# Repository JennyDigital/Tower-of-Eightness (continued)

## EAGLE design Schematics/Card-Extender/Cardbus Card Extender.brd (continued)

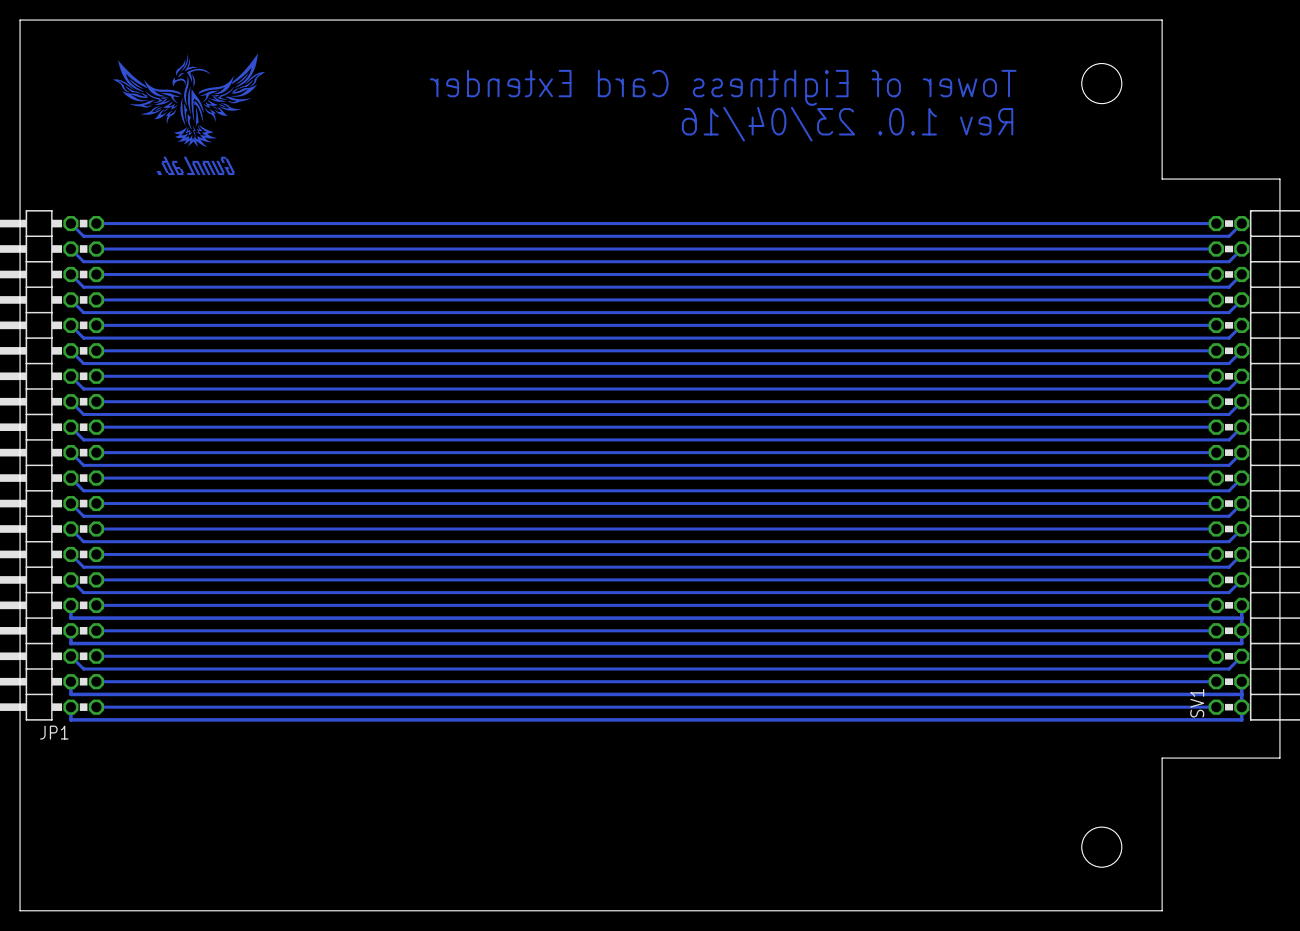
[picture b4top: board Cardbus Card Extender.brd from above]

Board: 2 copper layers, 125.7 x 88.9 mm, 3 parts (0 on the bottom side), 38 nets.

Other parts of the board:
U$1: LIONTECH

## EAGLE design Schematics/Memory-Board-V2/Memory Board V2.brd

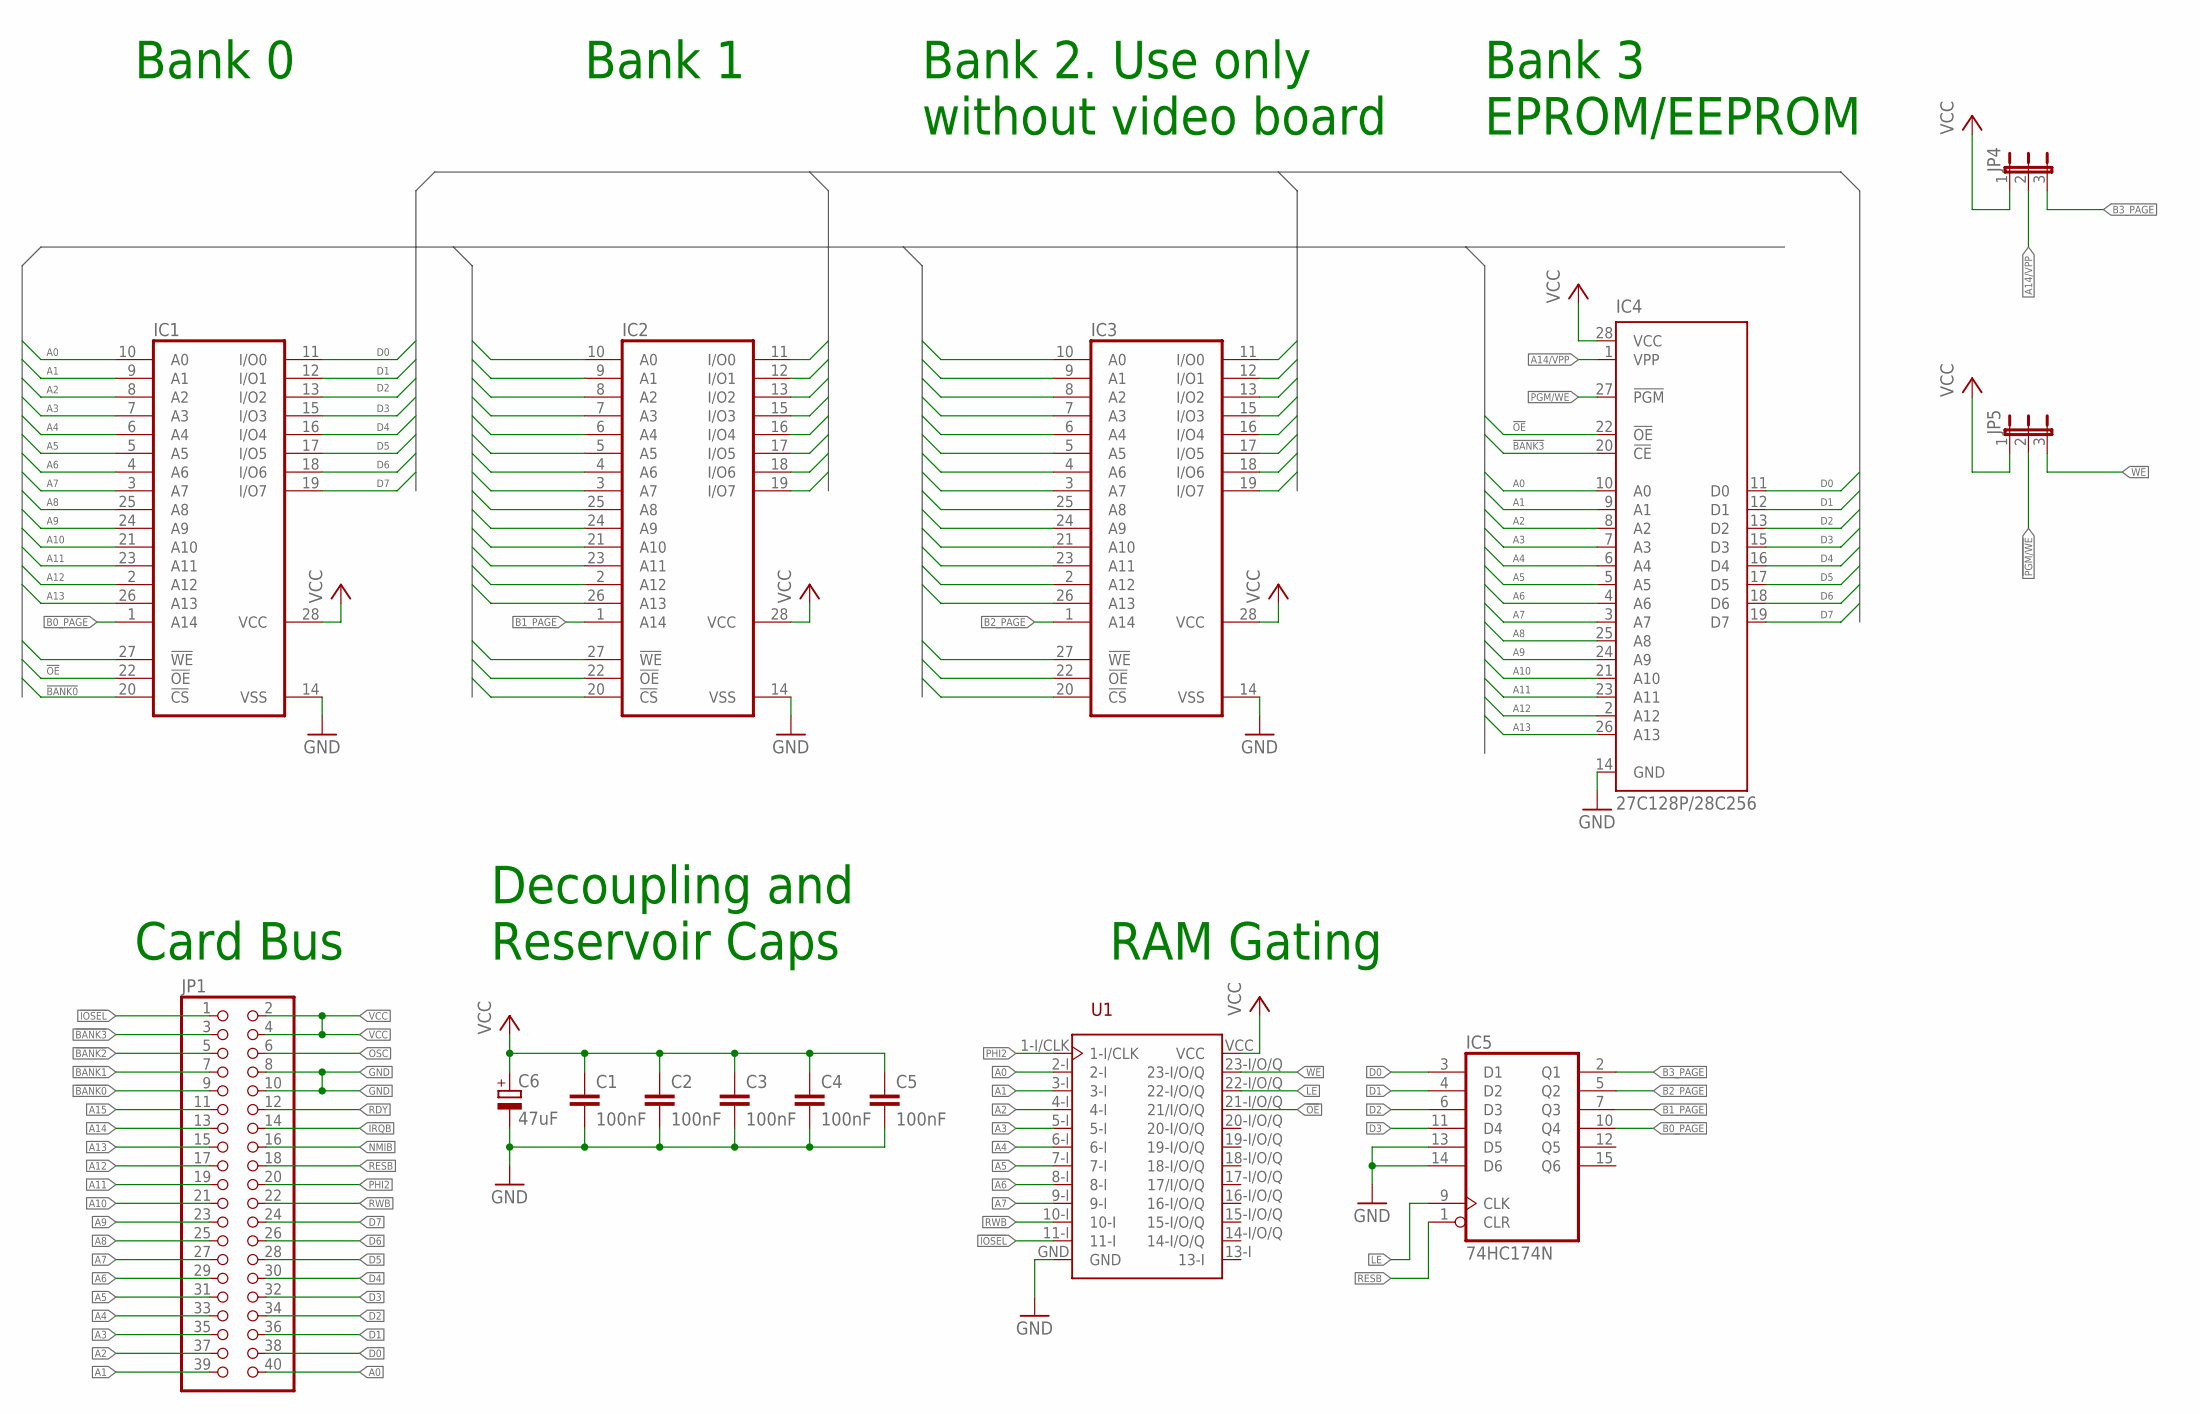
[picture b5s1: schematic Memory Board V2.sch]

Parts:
C1, C2, C3, C4, C5: 100nF; C050-025X075
C6: 47uF; E2,5-7
IC1, IC2, IC3: 62256P; DIL28-6
IC4: 27C128P/28C256; DIL28-6
IC5: 74HC174N; DIL16
JP1: PINHD-2X20/90; 2X20/90
JP4, JP5: JP2E; JP2
U1: GAL22V10D-DIP; DIP24

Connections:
!BANK0: IC1.20 (!CS), JP1.9
!BANK1: IC2.20 (!CS), JP1.7
!BANK2: IC3.20 (!CS), JP1.5
!BANK3: IC4.20 (!CE), JP1.3
!IOSEL: JP1.1, U1.11-I
!OE: IC1.22 (!OE), IC2.22 (!OE), IC3.22 (!OE), IC4.22 (!OE), U1.21-I/O/Q (21/I/O/Q)
!PGM/WE: IC4.27 (!PGM), JP5.2
!WE: IC1.27 (!WE), IC2.27 (!WE), IC3.27 (!WE), JP5.3, U1.23-I/O/Q
A0: IC1.10 (A0), IC2.10 (A0), IC3.10 (A0), IC4.10 (A0), JP1.40, U1.2-I
A1: IC1.9 (A1), IC2.9 (A1), IC3.9 (A1), IC4.9 (A1), JP1.39, U1.3-I
A2: IC1.8 (A2), IC2.8 (A2), IC3.8 (A2), IC4.8 (A2), JP1.37, U1.4-I
A3: IC1.7 (A3), IC2.7 (A3), IC3.7 (A3), IC4.7 (A3), JP1.35, U1.5-I
A4: IC1.6 (A4), IC2.6 (A4), IC3.6 (A4), IC4.6 (A4), JP1.33, U1.6-I
A5: IC1.5 (A5), IC2.5 (A5), IC3.5 (A5), IC4.5 (A5), JP1.31, U1.7-I
A6: IC1.4 (A6), IC2.4 (A6), IC3.4 (A6), IC4.4 (A6), JP1.29, U1.8-I
A7: IC1.3 (A7), IC2.3 (A7), IC3.3 (A7), IC4.3 (A7), JP1.27, U1.9-I
A8: IC1.25 (A8), IC2.25 (A8), IC3.25 (A8), IC4.25 (A8), JP1.25
A9: IC1.24 (A9), IC2.24 (A9), IC3.24 (A9), IC4.24 (A9), JP1.23
A10: IC1.21 (A10), IC2.21 (A10), IC3.21 (A10), IC4.21 (A10), JP1.21
A11: IC1.23 (A11), IC2.23 (A11), IC3.23 (A11), IC4.23 (A11), JP1.19
A12: IC1.2 (A12), IC2.2 (A12), IC3.2 (A12), IC4.2 (A12), JP1.17
A13: IC1.26 (A13), IC2.26 (A13), IC3.26 (A13), IC4.26 (A13), JP1.15
A14: JP1.13
A14/VPP: IC4.1 (VPP), JP4.2
A15: JP1.11
B0_PAGE: IC1.1 (A14), IC5.10 (Q4)
B1_PAGE: IC2.1 (A14), IC5.7 (Q3)
B2_PAGE: IC3.1 (A14), IC5.5 (Q2)
B3_PAGE: IC5.2 (Q1), JP4.3
D0: IC1.11 (I/O0), IC2.11 (I/O0), IC3.11 (I/O0), IC4.11 (D0), IC5.3 (D1), JP1.38
D1: IC1.12 (I/O1), IC2.12 (I/O1), IC3.12 (I/O1), IC4.12 (D1), IC5.4 (D2), JP1.36
D2: IC1.13 (I/O2), IC2.13 (I/O2), IC3.13 (I/O2), IC4.13 (D2), IC5.6 (D3), JP1.34
D3: IC1.15 (I/O3), IC2.15 (I/O3), IC3.15 (I/O3), IC4.15 (D3), IC5.11 (D4), JP1.32
D4: IC1.16 (I/O4), IC2.16 (I/O4), IC3.16 (I/O4), IC4.16 (D4), JP1.30
D5: IC1.17 (I/O5), IC2.17 (I/O5), IC3.17 (I/O5), IC4.17 (D5), JP1.28
D6: IC1.18 (I/O6), IC2.18 (I/O6), IC3.18 (I/O6), IC4.18 (D6), JP1.26
D7: IC1.19 (I/O7), IC2.19 (I/O7), IC3.19 (I/O7), IC4.19 (D7), JP1.24
GND: C1.2, C2.2, C3.2, C4.2, C5.2, C6.-, IC1.14 (VSS), IC2.14 (VSS), IC3.14 (VSS), IC4.14 (GND), IC5.8 (GND), IC5.13 (D5), IC5.14 (D6), JP1.8, JP1.10, U1.GND
IRQB: JP1.14
LE: IC5.9 (CLK), U1.22-I/O/Q
NMIB: JP1.16
OSC: JP1.6
PHI2: JP1.20, U1.1-I/CLK
RDY: JP1.12
RESB: IC5.1 (CLR), JP1.18
RWB: JP1.22, U1.10-I
VCC: C1.1, C2.1, C3.1, C4.1, C5.1, C6.+, IC1.28 (VCC), IC2.28 (VCC), IC3.28 (VCC), IC4.28 (VCC), IC5.16 (VCC), JP1.2, JP1.4, JP4.1, JP5.1, U1.VCC

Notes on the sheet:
Card Bus
Bank 0
Bank 3 EPROM/EEPROM
Bank 1
Bank 2. Use only without video board
Decoupling and Reservoir Caps
RAM Gating

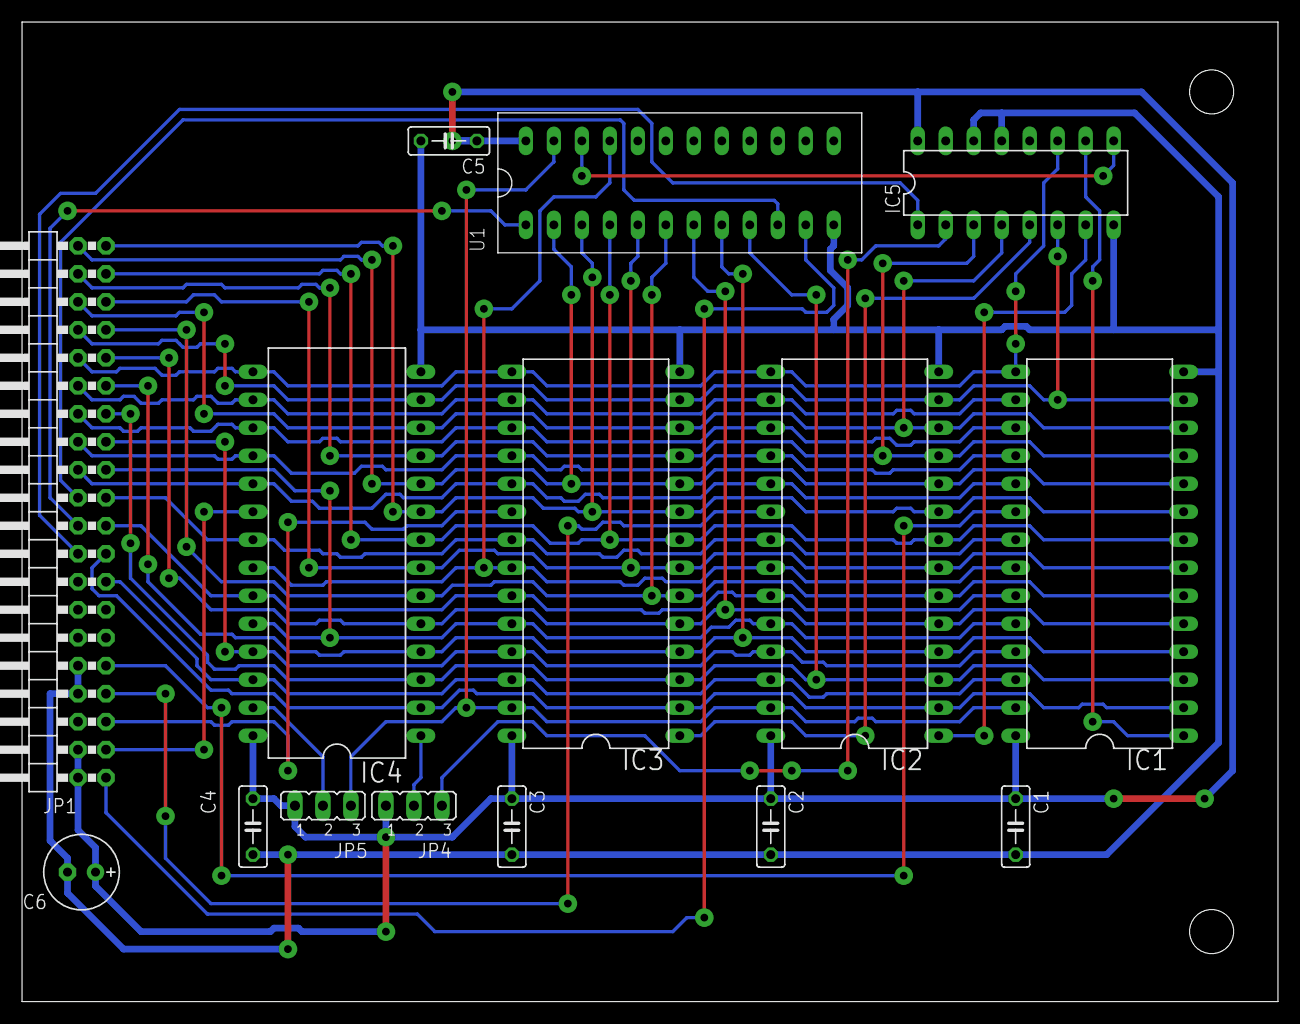
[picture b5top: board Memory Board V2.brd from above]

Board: 2 copper layers, 114.0 x 88.9 mm, 15 parts (0 on the bottom side), 41 nets.

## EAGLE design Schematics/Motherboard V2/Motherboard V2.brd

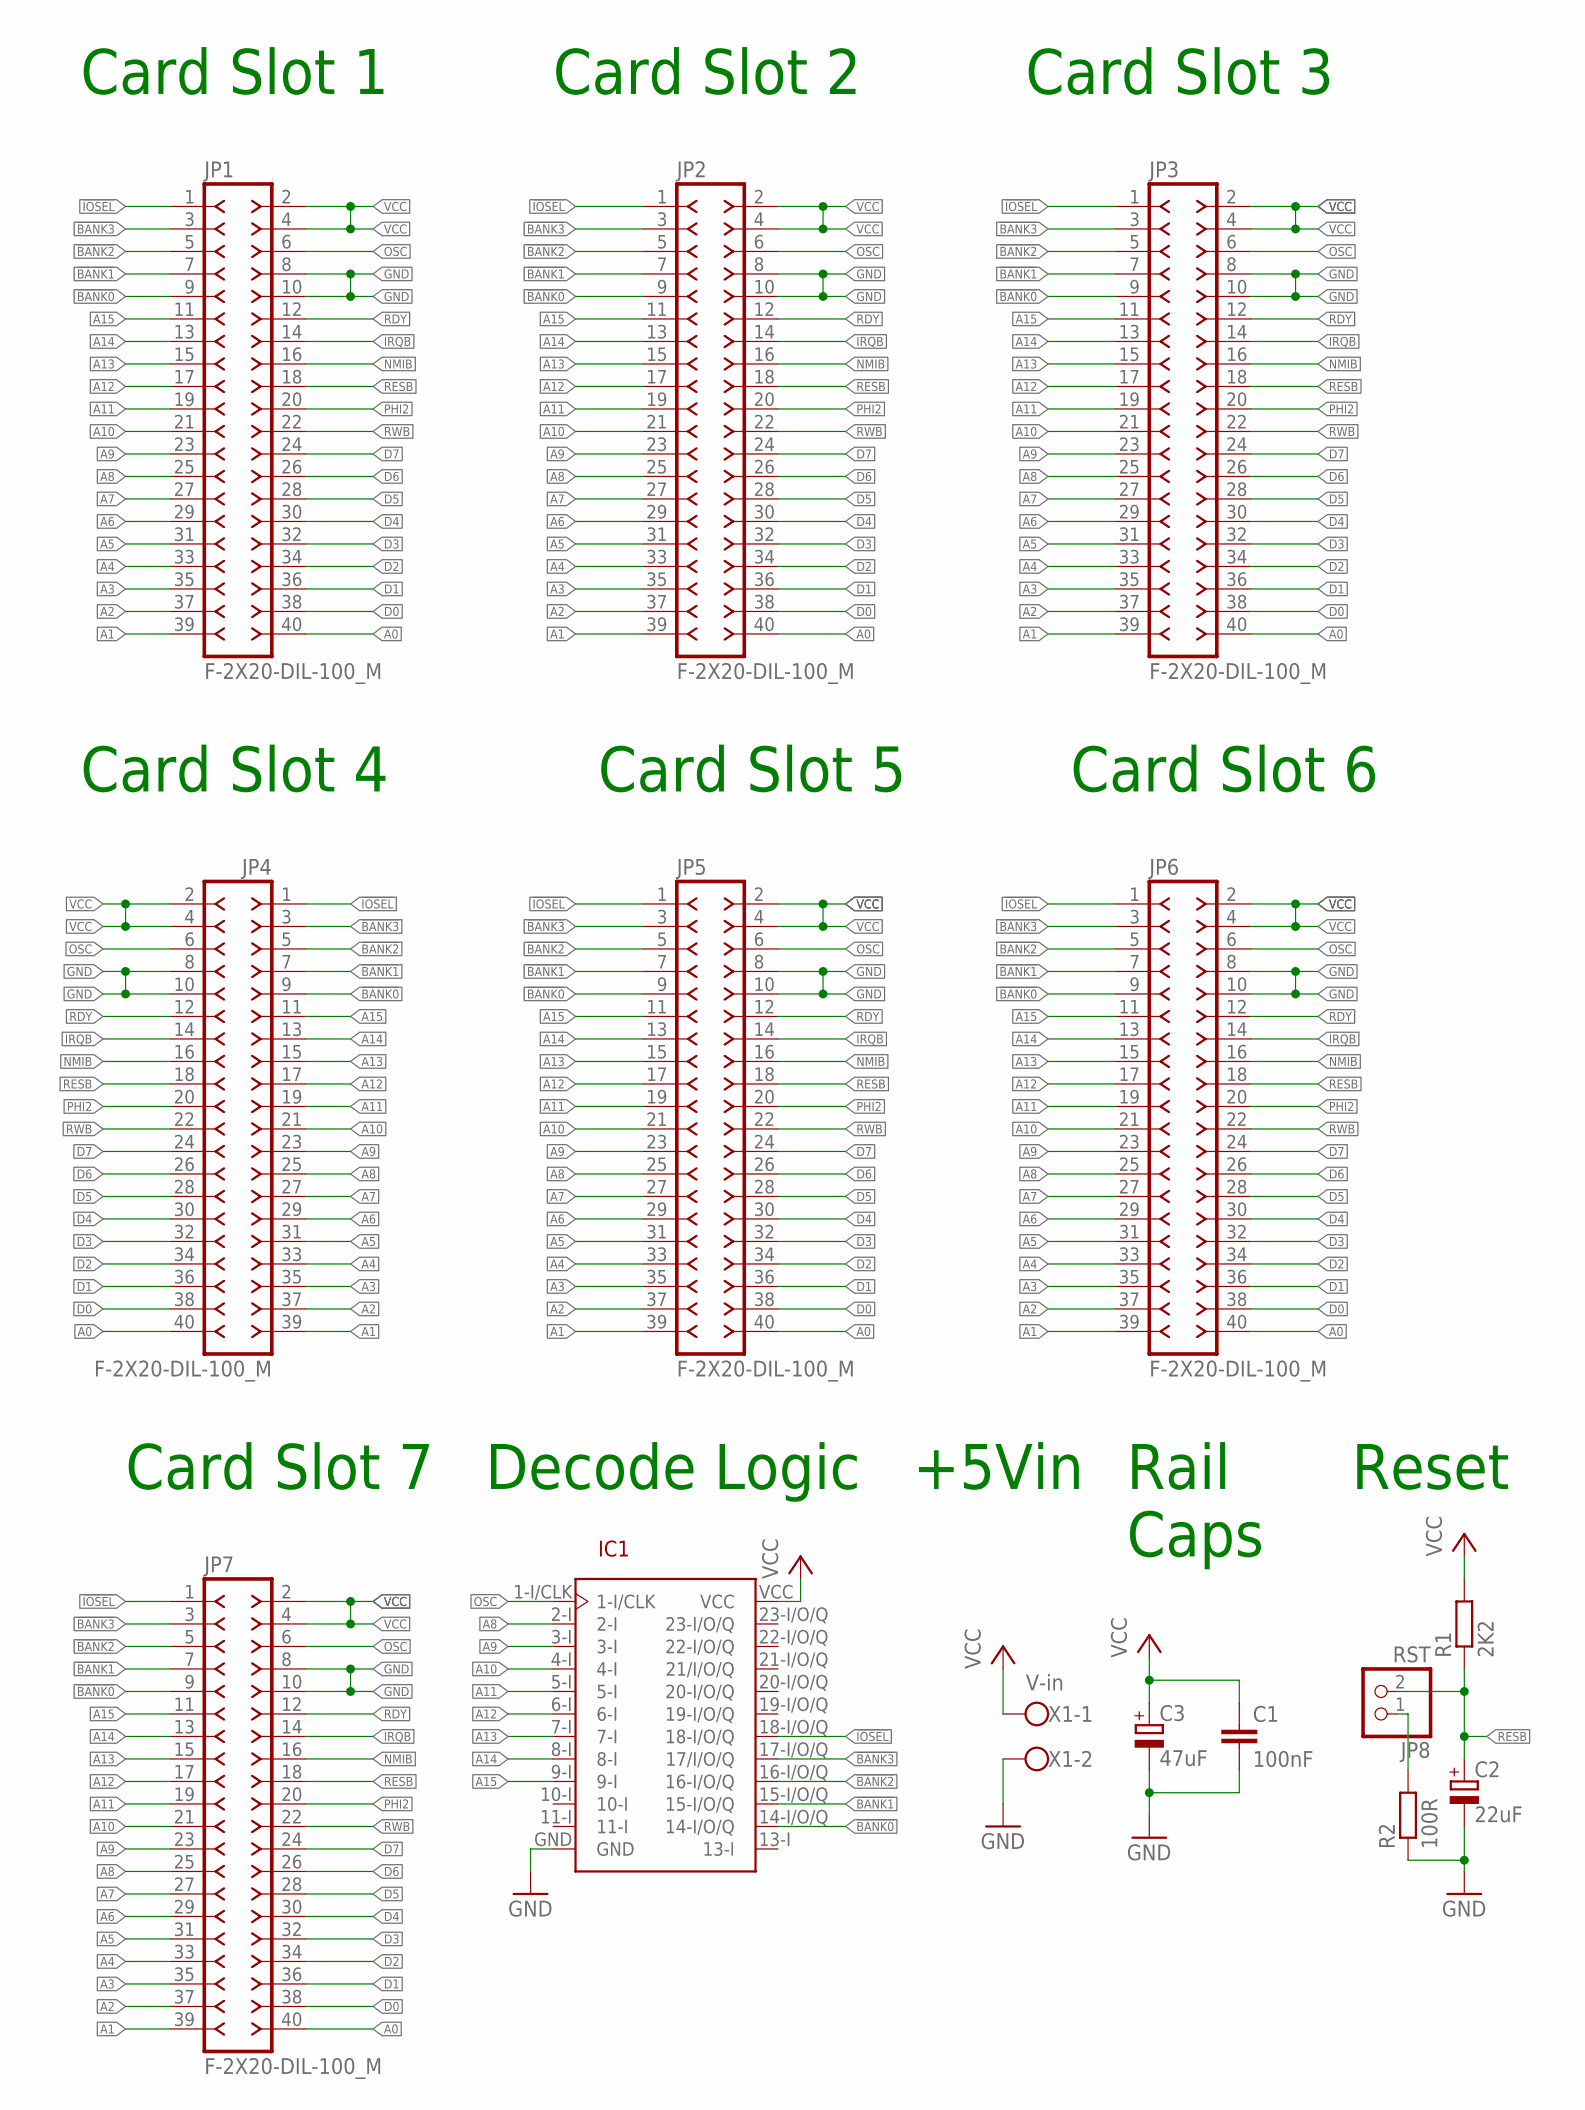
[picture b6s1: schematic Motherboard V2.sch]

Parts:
C1: 100nF; C050-025X075
C2: 22uF; E2-5
C3: 47uF; E2,5-7
IC1: GAL22V10D-DIP; DIP24
JP1, JP2, JP3, JP4, JP5, JP6, JP7: F-2X20-DIL-100_M; DIL-100-2X20_M
JP8: RST; 1X02
R1: 2K2; 0207/10
R2: 100R; 0207/10
X1: V-in; W237-102

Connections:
!BANK0: IC1.14-I/O/Q, JP1.9, JP2.9, JP3.9, JP4.9, JP5.9, JP6.9, JP7.9
!BANK1: IC1.15-I/O/Q, JP1.7, JP2.7, JP3.7, JP4.7, JP5.7, JP6.7, JP7.7
!BANK2: IC1.16-I/O/Q, JP1.5, JP2.5, JP3.5, JP4.5, JP5.5, JP6.5, JP7.5
!BANK3: IC1.17-I/O/Q (17/I/O/Q), JP1.3, JP2.3, JP3.3, JP4.3, JP5.3, JP6.3, JP7.3
!IOSEL: IC1.18-I/O/Q, JP1.1, JP2.1, JP3.1, JP4.1, JP5.1, JP6.1, JP7.1
A0: JP1.40, JP2.40, JP3.40, JP4.40, JP5.40, JP6.40, JP7.40
A1: JP1.39, JP2.39, JP3.39, JP4.39, JP5.39, JP6.39, JP7.39
A2: JP1.37, JP2.37, JP3.37, JP4.37, JP5.37, JP6.37, JP7.37
A3: JP1.35, JP2.35, JP3.35, JP4.35, JP5.35, JP6.35, JP7.35
A4: JP1.33, JP2.33, JP3.33, JP4.33, JP5.33, JP6.33, JP7.33
A5: JP1.31, JP2.31, JP3.31, JP4.31, JP5.31, JP6.31, JP7.31
A6: JP1.29, JP2.29, JP3.29, JP4.29, JP5.29, JP6.29, JP7.29
A7: JP1.27, JP2.27, JP3.27, JP4.27, JP5.27, JP6.27, JP7.27
A8: IC1.2-I, JP1.25, JP2.25, JP3.25, JP4.25, JP5.25, JP6.25, JP7.25
A9: IC1.3-I, JP1.23, JP2.23, JP3.23, JP4.23, JP5.23, JP6.23, JP7.23
A10: IC1.4-I, JP1.21, JP2.21, JP3.21, JP4.21, JP5.21, JP6.21, JP7.21
A11: IC1.5-I, JP1.19, JP2.19, JP3.19, JP4.19, JP5.19, JP6.19, JP7.19
A12: IC1.6-I, JP1.17, JP2.17, JP3.17, JP4.17, JP5.17, JP6.17, JP7.17
A13: IC1.7-I, JP1.15, JP2.15, JP3.15, JP4.15, JP5.15, JP6.15, JP7.15
A14: IC1.8-I, JP1.13, JP2.13, JP3.13, JP4.13, JP5.13, JP6.13, JP7.13
A15: IC1.9-I, JP1.11, JP2.11, JP3.11, JP4.11, JP5.11, JP6.11, JP7.11
D0: JP1.38, JP2.38, JP3.38, JP4.38, JP5.38, JP6.38, JP7.38
D1: JP1.36, JP2.36, JP3.36, JP4.36, JP5.36, JP6.36, JP7.36
D2: JP1.34, JP2.34, JP3.34, JP4.34, JP5.34, JP6.34, JP7.34
D3: JP1.32, JP2.32, JP3.32, JP4.32, JP5.32, JP6.32, JP7.32
D4: JP1.30, JP2.30, JP3.30, JP4.30, JP5.30, JP6.30, JP7.30
D5: JP1.28, JP2.28, JP3.28, JP4.28, JP5.28, JP6.28, JP7.28
D6: JP1.26, JP2.26, JP3.26, JP4.26, JP5.26, JP6.26, JP7.26
D7: JP1.24, JP2.24, JP3.24, JP4.24, JP5.24, JP6.24, JP7.24
GND: C1.2, C2.-, C3.-, IC1.GND, JP1.8, JP1.10, JP2.8, JP2.10, JP3.8, JP3.10, JP4.8, JP4.10, JP5.8, JP5.10, JP6.8, JP6.10, JP7.8, JP7.10, R2.1, X1.2
IRQB: JP1.14, JP2.14, JP3.14, JP4.14, JP5.14, JP6.14, JP7.14
unnamed: JP8.1, R2.2
NMIB: JP1.16, JP2.16, JP3.16, JP4.16, JP5.16, JP6.16, JP7.16
OSC: IC1.1-I/CLK, JP1.6, JP2.6, JP3.6, JP4.6, JP5.6, JP6.6, JP7.6
PHI2: JP1.20, JP2.20, JP3.20, JP4.20, JP5.20, JP6.20, JP7.20
RDY: JP1.12, JP2.12, JP3.12, JP4.12, JP5.12, JP6.12, JP7.12
RESB: C2.+, JP1.18, JP2.18, JP3.18, JP4.18, JP5.18, JP6.18, JP7.18, JP8.2, R1.1
RWB: JP1.22, JP2.22, JP3.22, JP4.22, JP5.22, JP6.22, JP7.22
VCC: C1.1, C3.+, IC1.VCC, JP1.2, JP1.4, JP2.2, JP2.4, JP3.2, JP3.4, JP4.2, JP4.4, JP5.2, JP5.4, JP6.2, JP6.4, JP7.2, JP7.4, R1.2, X1.1

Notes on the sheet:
Decode Logic
Card Slot 1
Card Slot 2
Card Slot 3
Card Slot 4
Reset
+5Vin
Rail Caps
Card Slot 5
Card Slot 6
Card Slot 7

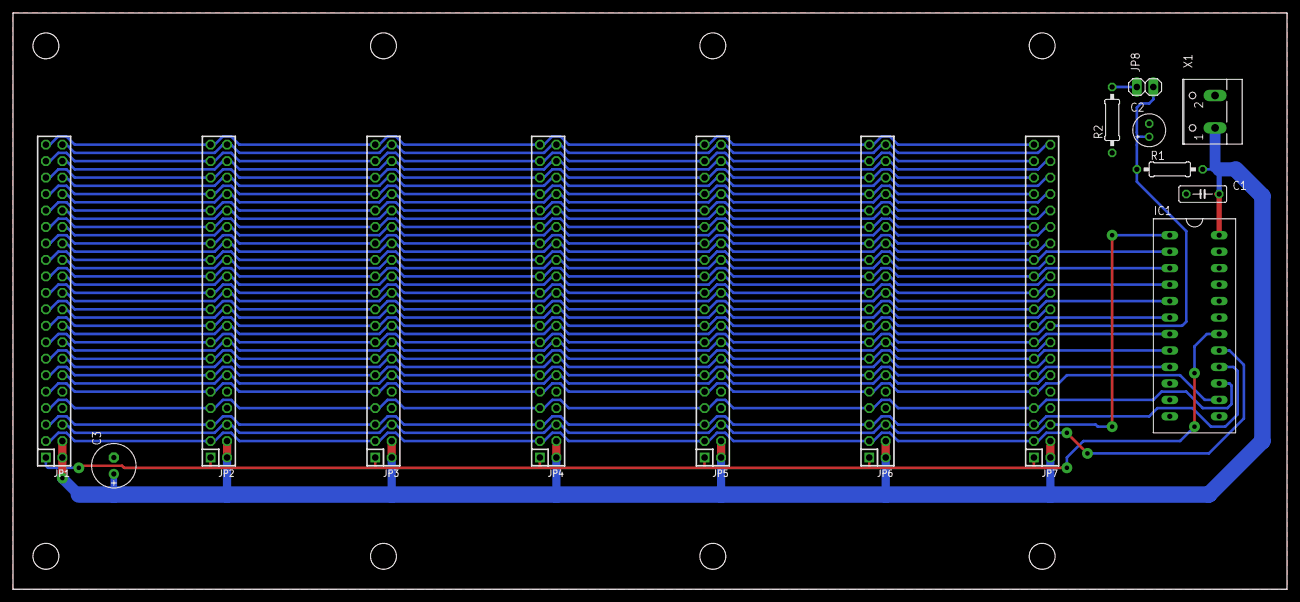
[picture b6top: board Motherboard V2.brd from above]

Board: 2 copper layers, 196.5 x 88.9 mm, 15 parts (0 on the bottom side), 39 nets.

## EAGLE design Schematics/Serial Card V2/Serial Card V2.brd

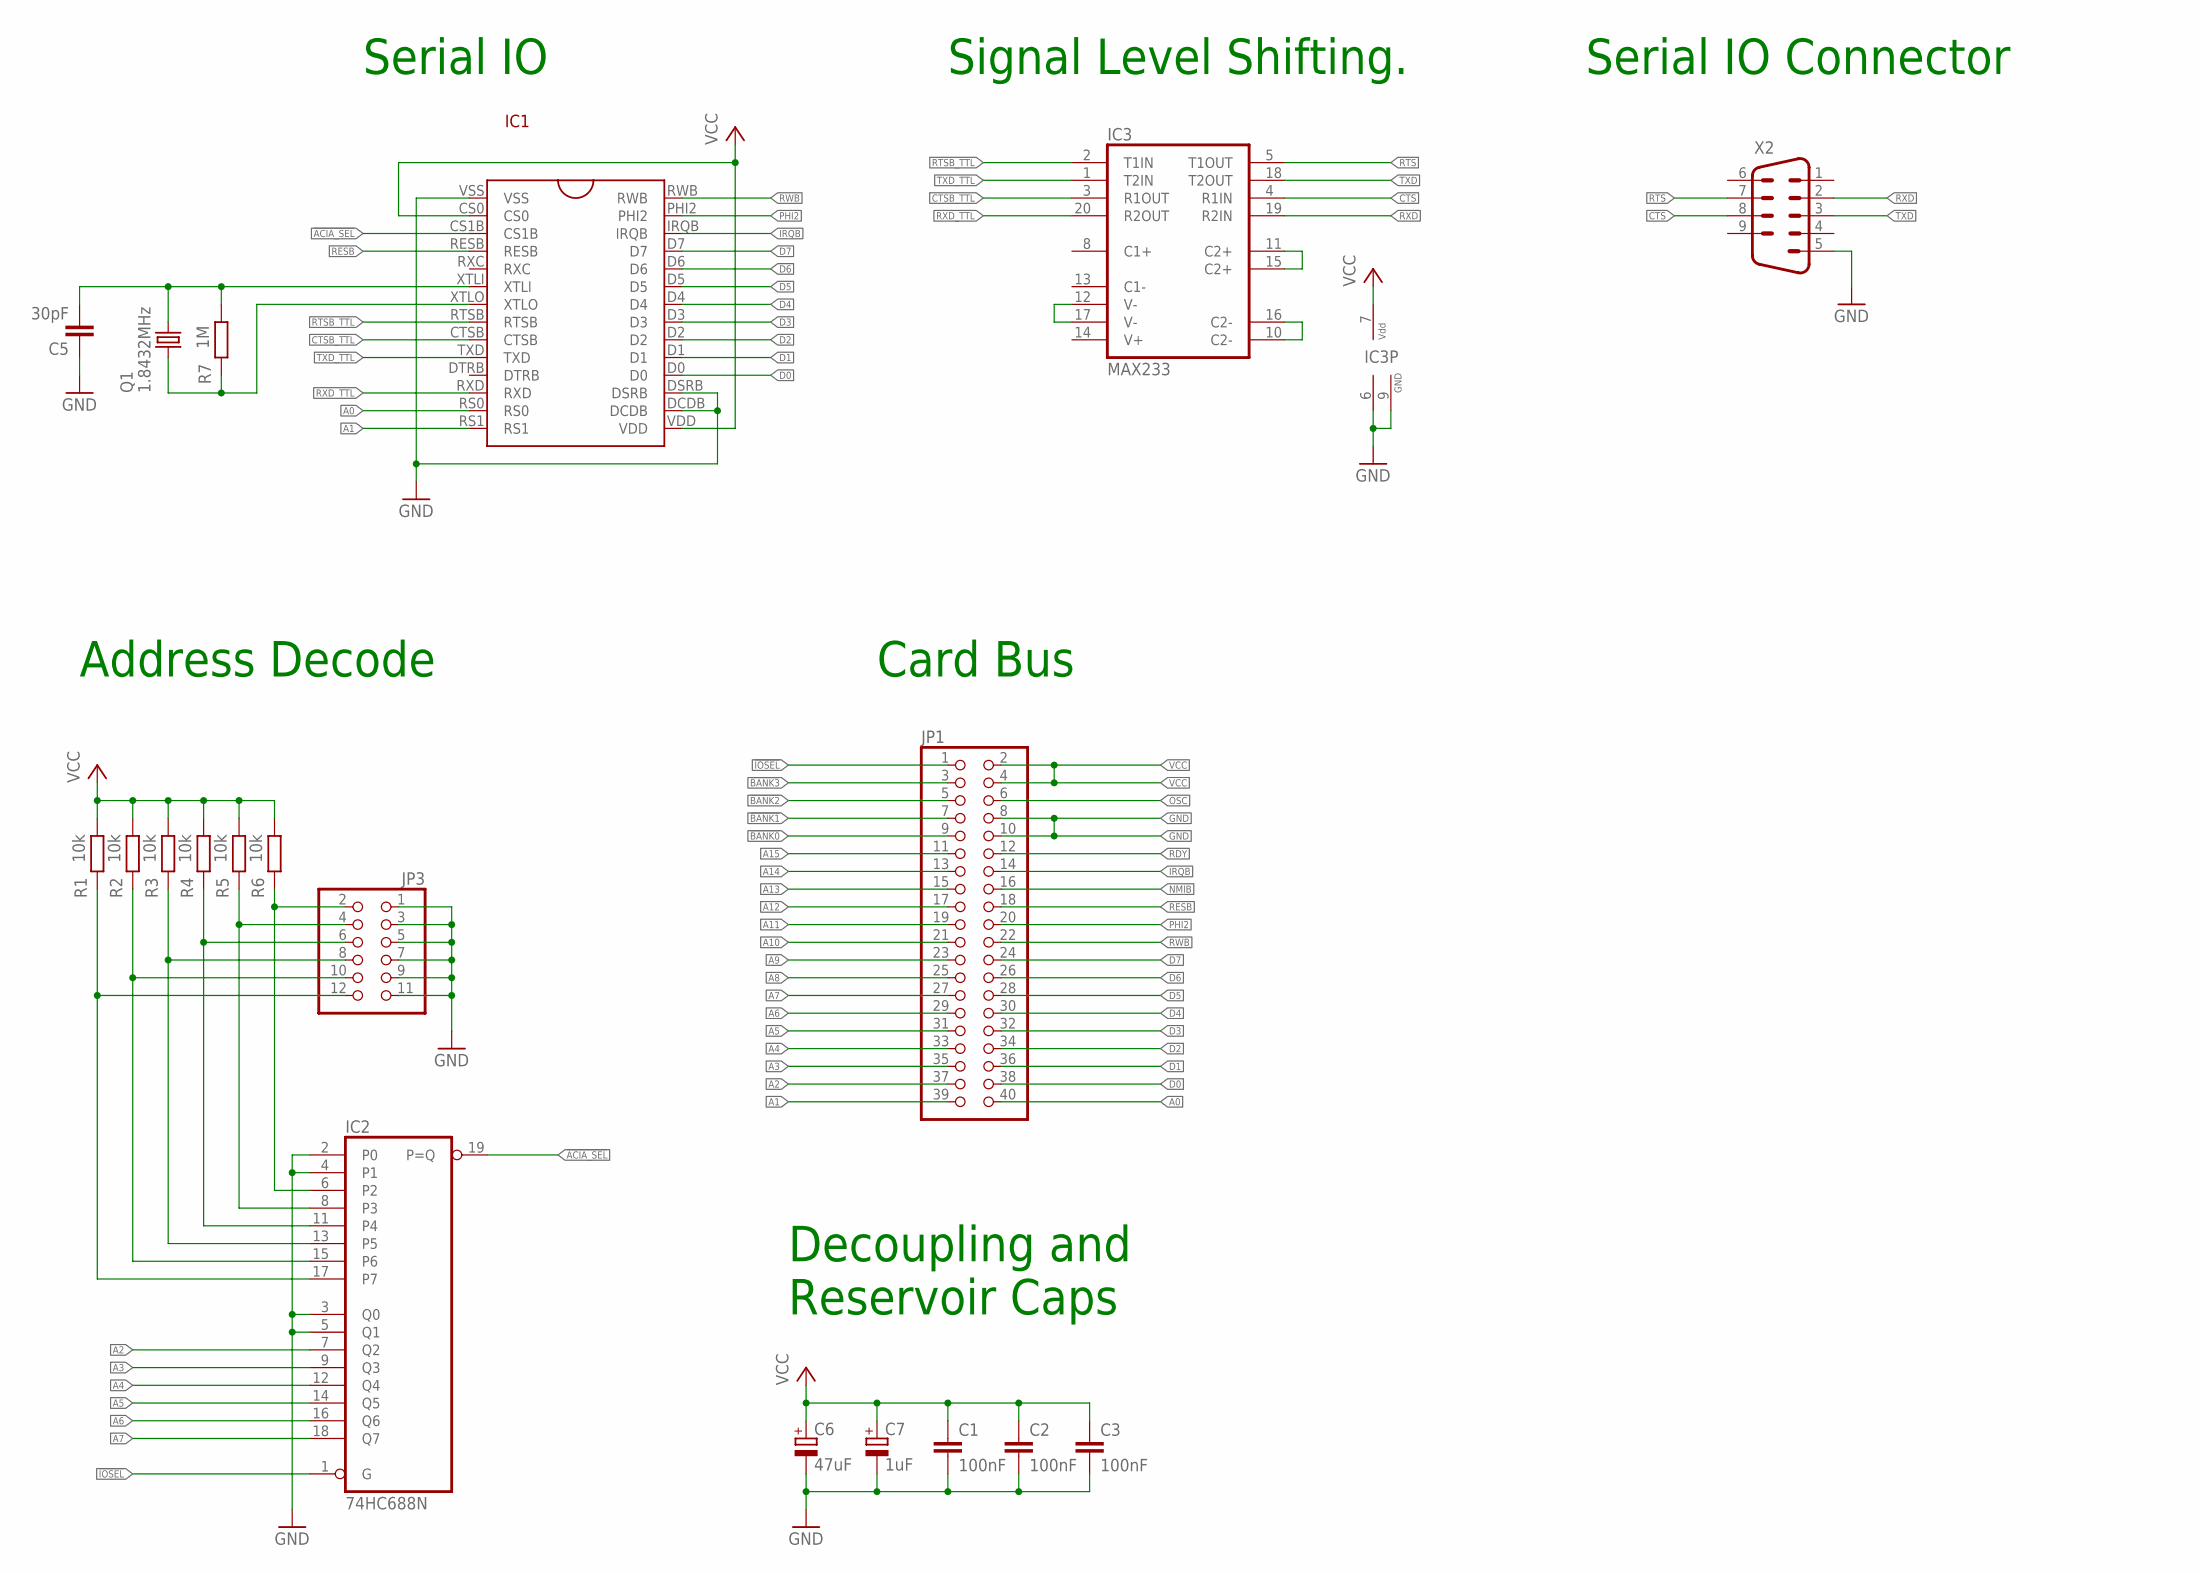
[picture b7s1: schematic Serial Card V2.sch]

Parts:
C1, C2, C3: 100nF; C050-025X075
C5: 30pF; C050-025X075
C6: 47uF; E2,5-7
C7: 1uF; E2,5-5
IC1: W65C51N-DIP
IC2: 74HC688N; DIL20
IC3: MAX233; DIL20
JP1: PINHD-2X20/90; 2X20/90
JP3: PINHD-2X6; 2X06
Q1: 1.8432MHz; HC49/S
R1, R2, R3, R4, R5, R6: 10k; 0207/2V
R7: 1M; 0207/2V
X2: M09HP

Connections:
!ACIA_SEL: IC1.CS1B, IC2.19 (P=Q)
!BANK0: JP1.9
!BANK1: JP1.7
!BANK2: JP1.5
!BANK3: JP1.3
!IOSEL: IC2.1 (G), JP1.1
A0: IC1.RS0, JP1.40
A1: IC1.RS1, JP1.39
A2: IC2.7 (Q2), JP1.37
A3: IC2.9 (Q3), JP1.35
A4: IC2.12 (Q4), JP1.33
A5: IC2.14 (Q5), JP1.31
A6: IC2.16 (Q6), JP1.29
A7: IC2.18 (Q7), JP1.27
A8: JP1.25
A9: JP1.23
A10: JP1.21
A11: JP1.19
A12: JP1.17
A13: JP1.15
A14: JP1.13
A15: JP1.11
CTS: IC3.4 (R1IN), X2.8
CTSB_TTL: IC1.CTSB, IC3.3 (R1OUT)
D0: IC1.D0, JP1.38
D1: IC1.D1, JP1.36
D2: IC1.D2, JP1.34
D3: IC1.D3, JP1.32
D4: IC1.D4, JP1.30
D5: IC1.D5, JP1.28
D6: IC1.D6, JP1.26
D7: IC1.D7, JP1.24
GND: C1.2, C2.2, C3.2, C5.1, C6.-, C7.-, IC1.DCDB, IC1.DSRB, IC1.VSS, IC2.2 (P0), IC2.3 (Q0), IC2.4 (P1), IC2.5 (Q1), IC2.10 (GND), IC3.6 (GND), IC3.9 (GND), JP1.8, JP1.10, JP3.1, JP3.3, JP3.5, JP3.7, JP3.9, JP3.11, X2.5
IRQB: IC1.IRQB, JP1.14
unnamed: C5.2, IC1.XTLI, Q1.2, R7.2
unnamed: IC1.XTLO, Q1.1, R7.1
unnamed: IC3.12 (V-), IC3.17 (V-)
unnamed: IC3.11 (C2+), IC3.15 (C2+)
unnamed: IC3.10 (C2-), IC3.16 (C2-)
NMIB: JP1.16
OSC: JP1.6
P2: IC2.6 (P2), JP3.2, R6.1
P3: IC2.8 (P3), JP3.4, R5.1
P4: IC2.11 (P4), JP3.6, R4.1
P5: IC2.13 (P5), JP3.8, R3.1
P6: IC2.15 (P6), JP3.10, R2.1
P7: IC2.17 (P7), JP3.12, R1.1
PHI2: IC1.PHI2, JP1.20
RDY: JP1.12
RESB: IC1.RESB, JP1.18
RTS: IC3.5 (T1OUT), X2.7
RTSB_TTL: IC1.RTSB, IC3.2 (T1IN)
RWB: IC1.RWB, JP1.22
RXD: IC3.19 (R2IN), X2.2
RXD_TTL: IC1.RXD, IC3.20 (R2OUT)
TXD: IC3.18 (T2OUT), X2.3
TXD_TTL: IC1.TXD, IC3.1 (T2IN)
VCC: C1.1, C2.1, C3.1, C6.+, C7.+, IC1.CS0, IC1.VDD, IC2.20 (VCC), IC3.7 (VDD), JP1.2, JP1.4, R1.2, R2.2, R3.2, R4.2, R5.2, R6.2

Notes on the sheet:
Card Bus
Decoupling and Reservoir Caps
Address Decode
Serial IO
Signal Level Shifting.
Serial IO Connector

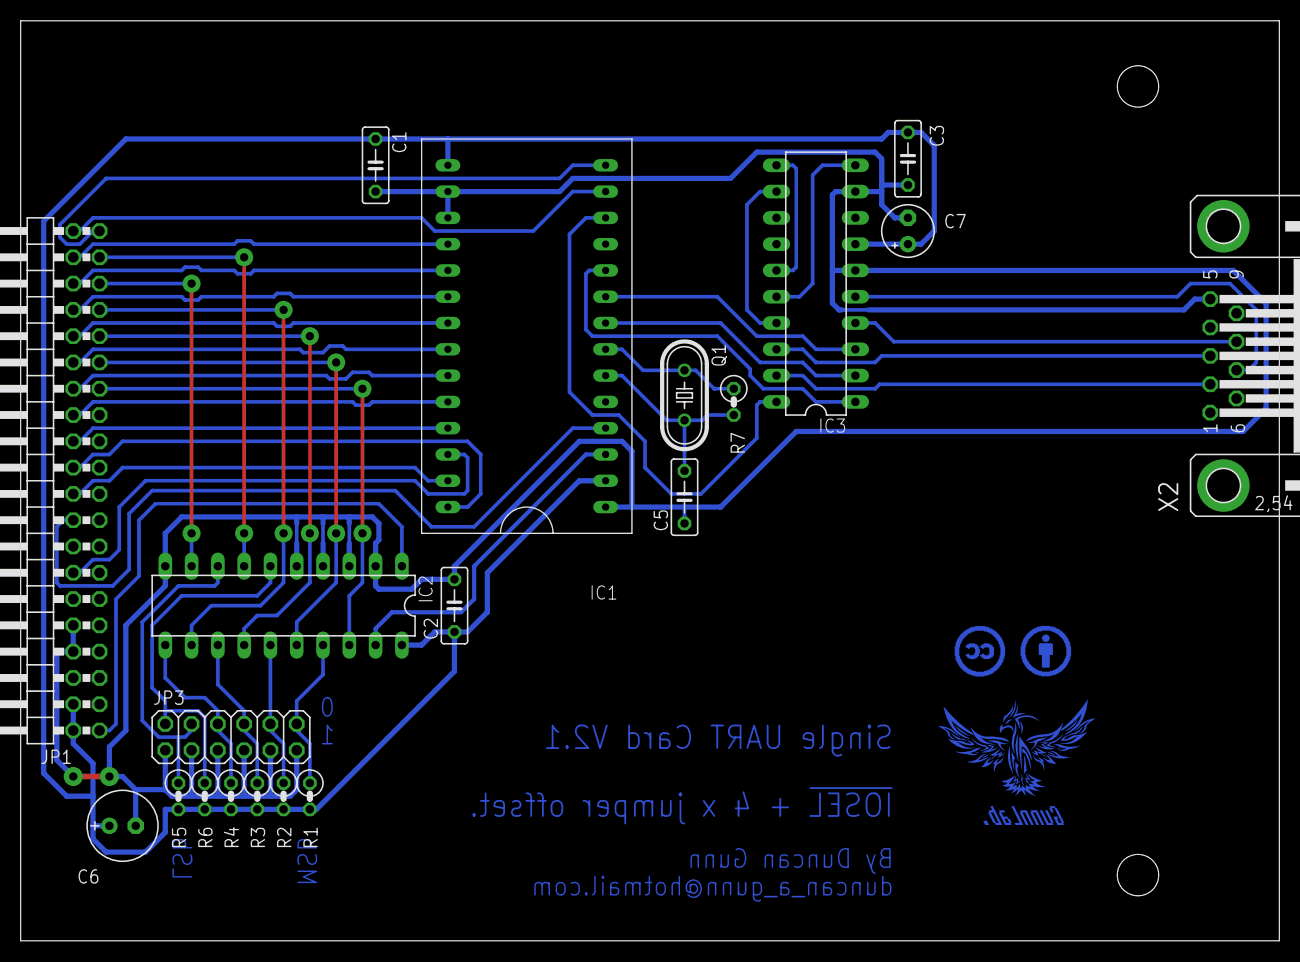
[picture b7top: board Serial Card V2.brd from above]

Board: 2 copper layers, 121.6 x 88.9 mm, 23 parts (0 on the bottom side), 43 nets.

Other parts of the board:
U$1: LIONTECH
U$2: BY
U$3: CC
